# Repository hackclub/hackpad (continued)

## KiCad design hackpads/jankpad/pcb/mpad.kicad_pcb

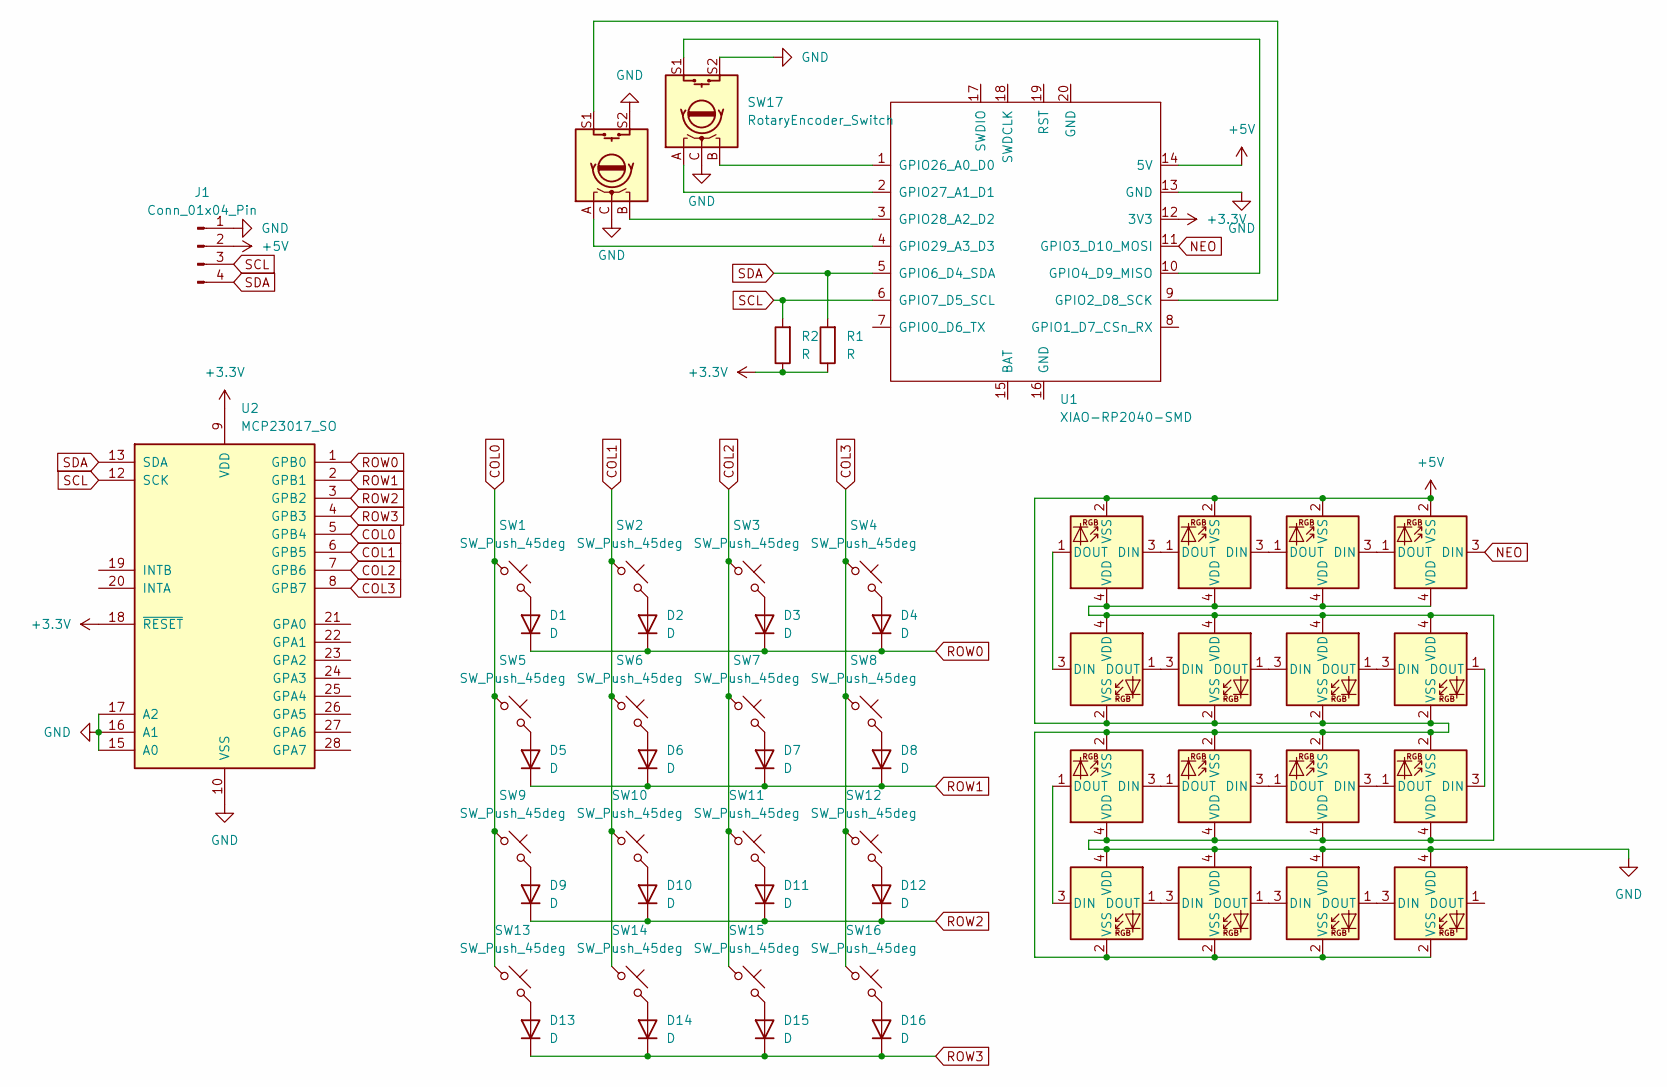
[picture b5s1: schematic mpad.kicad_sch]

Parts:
D1, D2, D3, D4, D5, D6, D7, D8, D9, D10, D11, D12, D13, D14, D15, D16: D; D_DO-35_SOD27_P7.62mm_Horizontal
D17, D18, D19, D20, D21, D22, D23, D24, D25, D26, D27, D28, D29, D30, D31, D32: SK6812MINI; GoofyLED
J1: Conn_01x04_Pin; SSD1306-0.91-OLED-4pin-128x32
R1, R2: R; R_Axial_DIN0204_L3.6mm_D1.6mm_P7.62mm_Horizontal
SW1, SW2, SW3, SW4, SW5, SW6, SW7, SW8, SW9, SW10, SW11, SW12, SW13, SW14, SW15, SW16: SW_Push_45deg; CustomSwitch
SW17, SW18: RotaryEncoder_Switch; RotaryEncoder_Alps_EC11E-Switch_Vertical_H20mm_CircularMoun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
U1: XIAO-RP2040-SMD
U2: MCP23017_SO; SOIC-28W_7.5x17.9mm_P1.27mm

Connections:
+3.3V: R1.1, R2.1, U1.12 (3V3), U2.9 (VDD), U2.18 (~RESET)
+5V: D17.2 (VSS), D18.2 (VSS), D19.2 (VSS), D20.2 (VSS), D21.2 (VSS), D22.2 (VSS), D23.2 (VSS), D24.2 (VSS), D25.2 (VSS), D26.2 (VSS), D27.2 (VSS), D28.2 (VSS), D29.2 (VSS), D30.2 (VSS), D31.2 (VSS), D32.2 (VSS), J1.2, U1.14 (5V)
COL0: SW1.1, SW5.1, SW9.1, SW13.1, U2.5 (GPB4)
COL1: SW2.1, SW6.1, SW10.1, SW14.1, U2.6 (GPB5)
COL2: SW3.1, SW7.1, SW11.1, SW15.1, U2.7 (GPB6)
COL3: SW4.1, SW8.1, SW12.1, SW16.1, U2.8 (GPB7)
GND: D17.4 (VDD), D18.4 (VDD), D19.4 (VDD), D20.4 (VDD), D21.4 (VDD), D22.4 (VDD), D23.4 (VDD), D24.4 (VDD), D25.4 (VDD), D26.4 (VDD), D27.4 (VDD), D28.4 (VDD), D29.4 (VDD), D30.4 (VDD), D31.4 (VDD), D32.4 (VDD), J1.1, SW17.C, SW17.S2, SW18.C, SW18.S2, U1.13 (GND), U2.10 (VSS), U2.15 (A0), U2.16 (A1), U2.17 (A2)
NEO: D17.3 (DIN), U1.11 (GPIO3_D10_MOSI)
unnamed: D1.2 (A), SW1.2
unnamed: D2.2 (A), SW2.2
unnamed: D3.2 (A), SW3.2
unnamed: D4.2 (A), SW4.2
unnamed: D5.2 (A), SW5.2
unnamed: D6.2 (A), SW6.2
unnamed: D7.2 (A), SW7.2
unnamed: D8.2 (A), SW8.2
unnamed: D9.2 (A), SW9.2
unnamed: D10.2 (A), SW10.2
unnamed: D11.2 (A), SW11.2
unnamed: D12.2 (A), SW12.2
unnamed: D13.2 (A), SW13.2
unnamed: D14.2 (A), SW14.2
unnamed: D15.2 (A), SW15.2
unnamed: D16.2 (A), SW16.2
unnamed: D17.1 (DOUT), D18.3 (DIN)
unnamed: D18.1 (DOUT), D19.3 (DIN)
unnamed: D19.1 (DOUT), D20.3 (DIN)
unnamed: D20.1 (DOUT), D21.3 (DIN)
unnamed: D21.1 (DOUT), D22.3 (DIN)
unnamed: D22.1 (DOUT), D23.3 (DIN)
unnamed: D23.1 (DOUT), D24.3 (DIN)
unnamed: D24.1 (DOUT), D25.3 (DIN)
unnamed: D25.1 (DOUT), D26.3 (DIN)
unnamed: D26.1 (DOUT), D27.3 (DIN)
unnamed: D27.1 (DOUT), D28.3 (DIN)
unnamed: D28.1 (DOUT), D29.3 (DIN)
unnamed: D29.1 (DOUT), D30.3 (DIN)
unnamed: D30.1 (DOUT), D31.3 (DIN)
unnamed: D31.1 (DOUT), D32.3 (DIN)
unnamed: SW18.S1, U1.9 (GPIO2_D8_SCK)
unnamed: SW17.S1, U1.10 (GPIO4_D9_MISO)
unnamed: SW17.B, U1.1 (GPIO26_A0_D0)
unnamed: SW17.A, U1.2 (GPIO27_A1_D1)
unnamed: SW18.B, U1.3 (GPIO28_A2_D2)
unnamed: SW18.A, U1.4 (GPIO29_A3_D3)
ROW0: D1.1 (K), D2.1 (K), D3.1 (K), D4.1 (K), U2.1 (GPB0)
ROW1: D5.1 (K), D6.1 (K), D7.1 (K), D8.1 (K), U2.2 (GPB1)
ROW2: D9.1 (K), D10.1 (K), D11.1 (K), D12.1 (K), U2.3 (GPB2)
ROW3: D13.1 (K), D14.1 (K), D15.1 (K), D16.1 (K), U2.4 (GPB3)
SCL: J1.3, R2.2, U1.6 (GPIO7_D5_SCL), U2.12 (SCK)
SDA: J1.4, R1.2, U1.5 (GPIO6_D4_SDA), U2.13 (SDA)

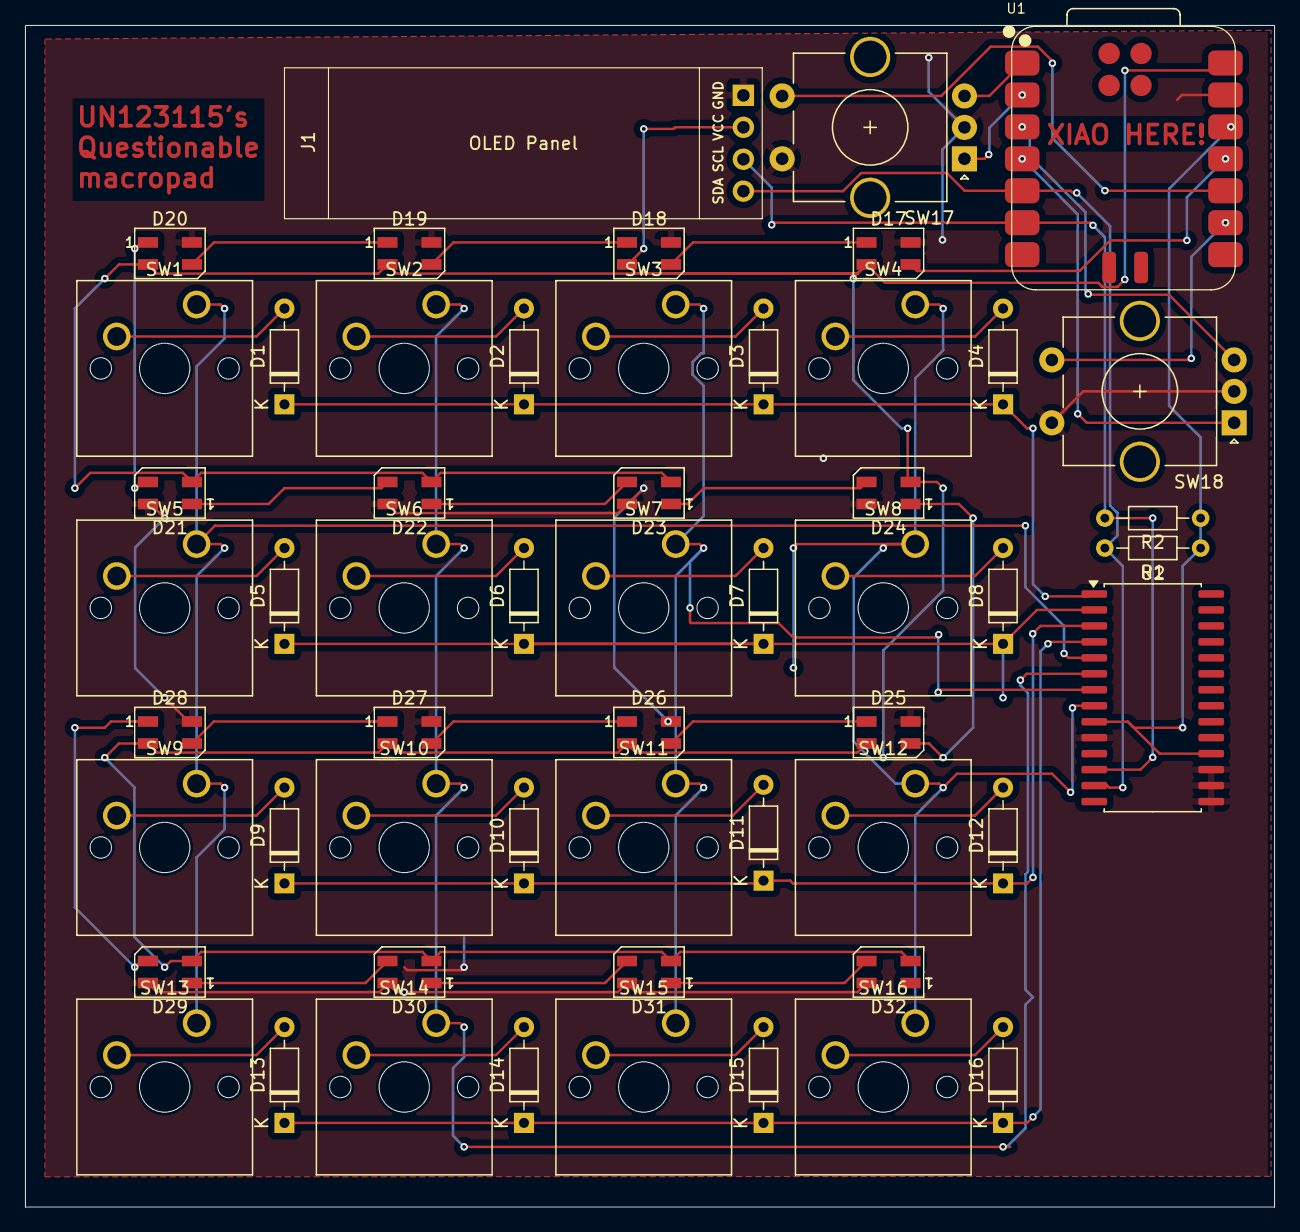
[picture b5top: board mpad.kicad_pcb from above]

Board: 2 copper layers, 99.3 x 94.0 mm, 55 parts (0 on the bottom side), 51 nets.

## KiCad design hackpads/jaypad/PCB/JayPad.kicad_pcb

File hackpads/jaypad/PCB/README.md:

## Components List
| Component                             | Quantity |
|---------------------------------------|----------|
| Cherry MX Switches (TBD in Slack DMs) | 12       |
| Kailh Sockets                         | 12       |
| 500ohm THT Resistor                   | 1        |
| EC11 Rotary Encoder                   | 1        |
| 1N4148W (SOD123)                      | 12       |
| Seeed Studio XIAO RP2040              | 1        |
| WS2812B                               | 8        |
## PCB
White PCB. Should look something like this:

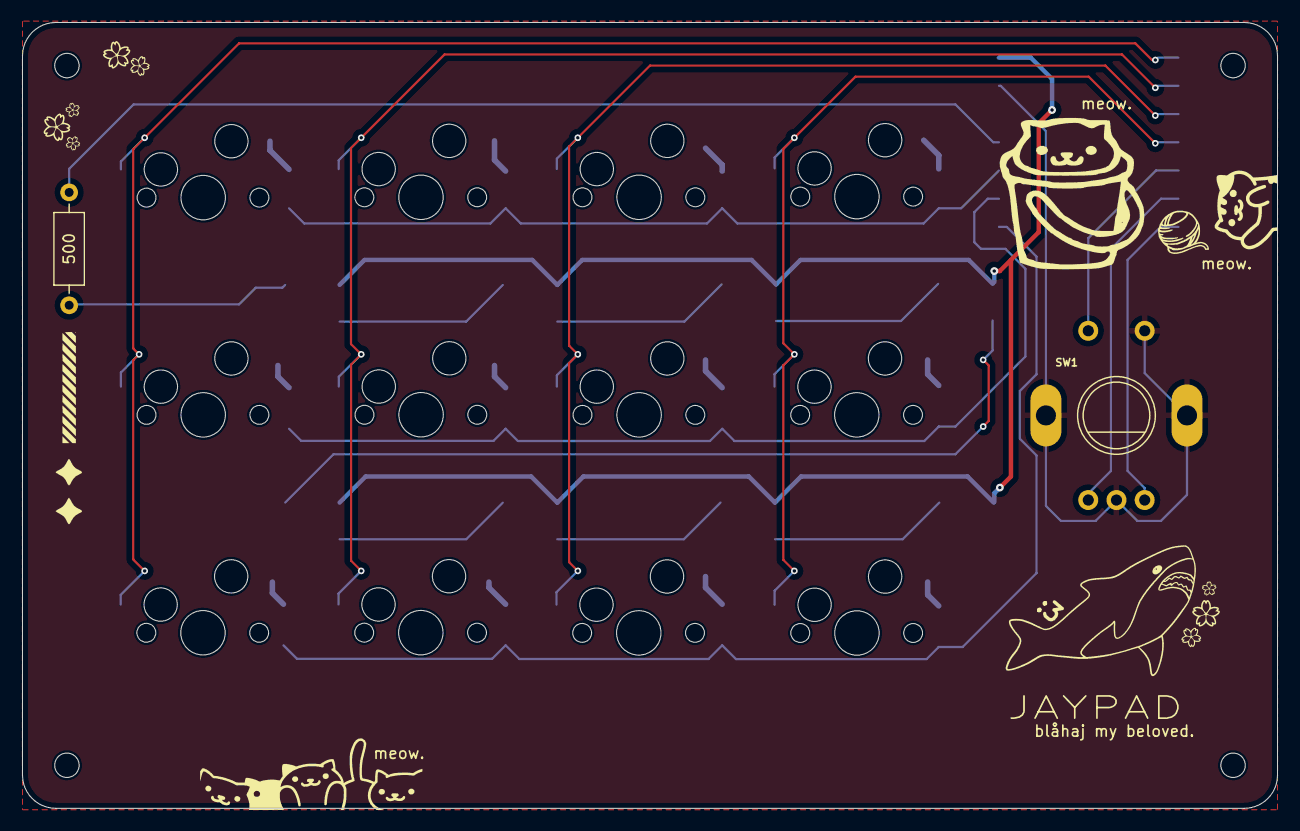
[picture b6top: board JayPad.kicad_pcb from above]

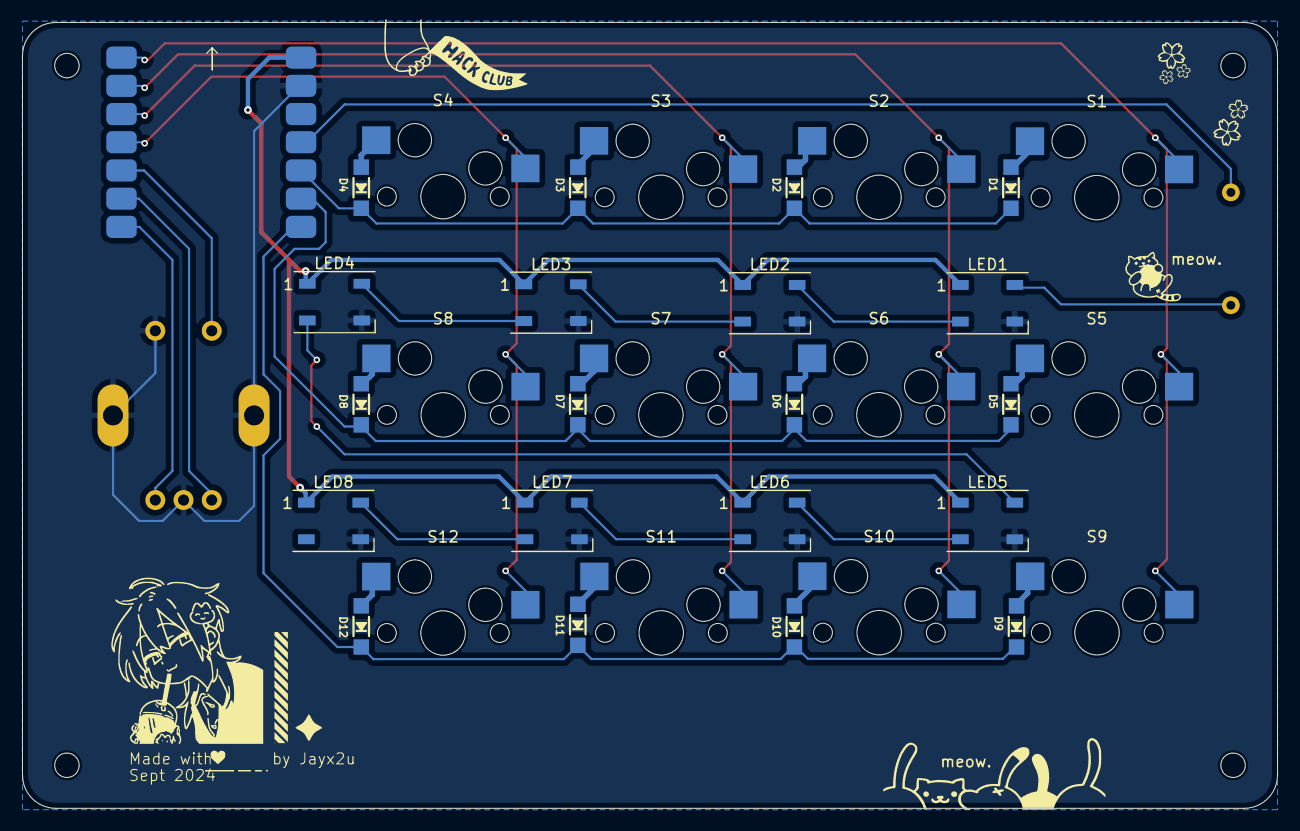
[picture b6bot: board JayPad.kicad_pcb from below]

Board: 2 copper layers, 113.0 x 70.8 mm, 36 parts (21 on the bottom side), 33 nets.

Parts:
:3: LOGO
D1, D2, D3, D4, D5, D6, D7, D8, D9, D10, D11, D12: 1N4148W; MICROBUILDER_SOD-123
LED1, LED2, LED3, LED4, LED5, LED6, LED7, LED8: WS2812B; LED_WS2812B_PLCC4_5.0x5.0mm_P3.2mm
M1: MOUDLE-SEEEDUINO-XIAO; MOUDLE14P-SMD-2.54-21X17.8MM
R1: 500; R_Axial_DIN0207_L6.3mm_D2.5mm_P10.16mm_Horizontal
S1, S2, S3, S4, S5, S6, S7, S8, S9, S10, S11, S12: CherryMX; CherryMX_1.00u_KailhSocket
SW1: PEC11-4215F-S24; ADAFRUIT_ELECTROMECH_PEC11+SWITCH

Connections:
+5V: LED1.1 (VDD), LED2.1 (VDD), LED3.1 (VDD), LED4.1 (VDD), LED5.1 (VDD), LED6.1 (VDD), LED7.1 (VDD), LED8.1 (VDD), M1.14 (5V)
COL0: M1.1 (PA02_A0_D0), S1.1, S5.1, S9.1
COL1: M1.2 (PA4_A1_D1), S2.1, S6.1, S10.1
COL2: M1.3 (PA10_A2_D2), S3.1, S7.1, S11.1
COL3: M1.4 (PA11_A3_D3), S4.1, S8.1, S12.1
DOUT0: LED4.2 (DOUT), LED5.4 (DIN)
ENC_A: M1.6 (PA9_A5_D5_SCL), SW1.P$A
ENC_B: M1.7 (PB08_A6_D6_TX), SW1.P$B
ENC_SW: M1.5 (PA8_A4_D4_SDA), SW1.P$1
GND: LED1.3 (VSS), LED2.3 (VSS), LED3.3 (VSS), LED4.3 (VSS), LED5.3 (VSS), LED6.3 (VSS), LED7.3 (VSS), LED8.3 (VSS), M1.13 (GND), SW1.P$2, SW1.P$C, SW1.P$GND1, SW1.P$GND2
unnamed: D1.A, S1.2
unnamed: D2.A, S2.2
unnamed: D3.A, S3.2
unnamed: D4.A, S4.2
unnamed: D5.A, S5.2
unnamed: D6.A, S6.2
unnamed: D7.A, S7.2
unnamed: D8.A, S8.2
unnamed: D9.A, S9.2
unnamed: D10.A, S10.2
unnamed: D11.A, S11.2
unnamed: D12.A, S12.2
unnamed: LED3.2 (DOUT), LED4.4 (DIN)
unnamed: LED2.2 (DOUT), LED3.4 (DIN)
unnamed: LED1.2 (DOUT), LED2.4 (DIN)
unnamed: LED1.4 (DIN), R1.2
unnamed: LED5.2 (DOUT), LED6.4 (DIN)
unnamed: LED6.2 (DOUT), LED7.4 (DIN)
unnamed: LED7.2 (DOUT), LED8.4 (DIN)
RGB: M1.11 (PA6_A10_D10_MOSI), R1.1
ROW0: D1.C, D2.C, D3.C, D4.C, M1.10 (PA5_A9_D9_MISO)
ROW1: D5.C, D6.C, D7.C, D8.C, M1.9 (PA7_A8_D8_SCK)
ROW2: D9.C, D10.C, D11.C, D12.C, M1.8 (PB09_A7_D7_RX)

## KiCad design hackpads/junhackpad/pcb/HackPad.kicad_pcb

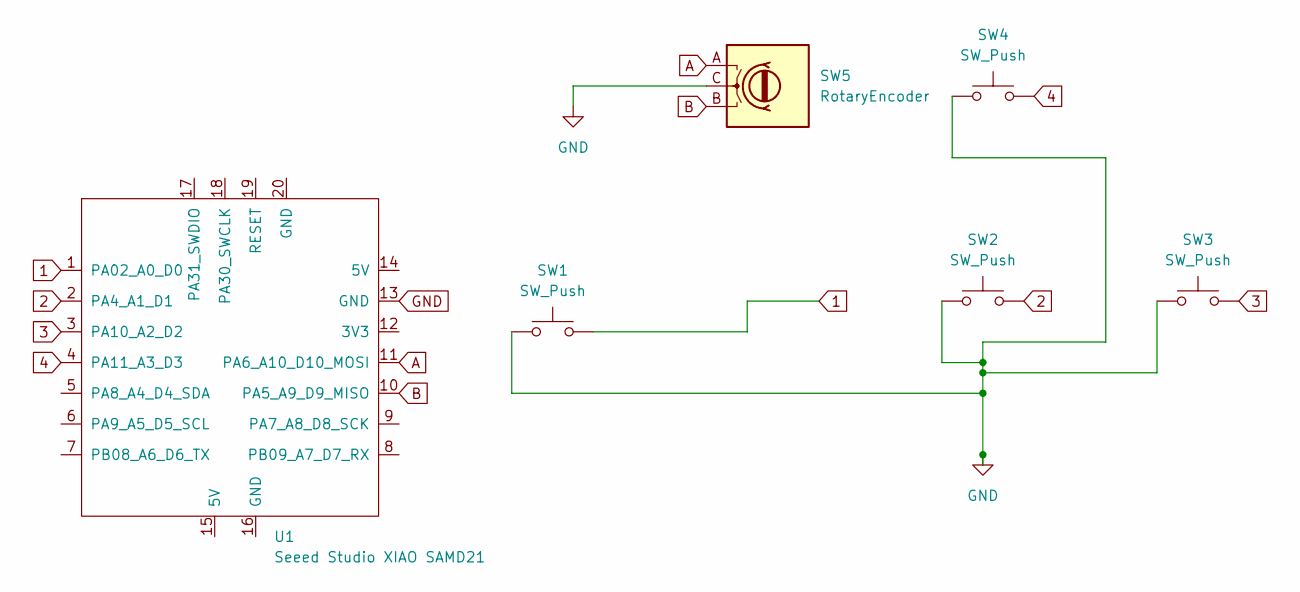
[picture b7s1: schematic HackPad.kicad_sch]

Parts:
SW1, SW2, SW3, SW4: SW_Push; SW_Cherry_MX_1.00u_PCB
SW5: RotaryEncoder; RotaryEncoder_Alps_EC11E-Switch_Vertical_H20mm
U1: Seeed Studio XIAO SAMD21; XIAO-Generic-Thruhole-14P-2.54-21X17.8MM

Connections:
1: SW1.2, U1.1 (PA02_A0_D0)
2: SW2.2, U1.2 (PA4_A1_D1)
3: SW3.2, U1.3 (PA10_A2_D2)
4: SW4.2, U1.4 (PA11_A3_D3)
A: SW5.A, U1.11 (PA6_A10_D10_MOSI)
B: SW5.B, U1.10 (PA5_A9_D9_MISO)
GND: SW1.1, SW2.1, SW3.1, SW4.1, SW5.C, U1.13 (GND)

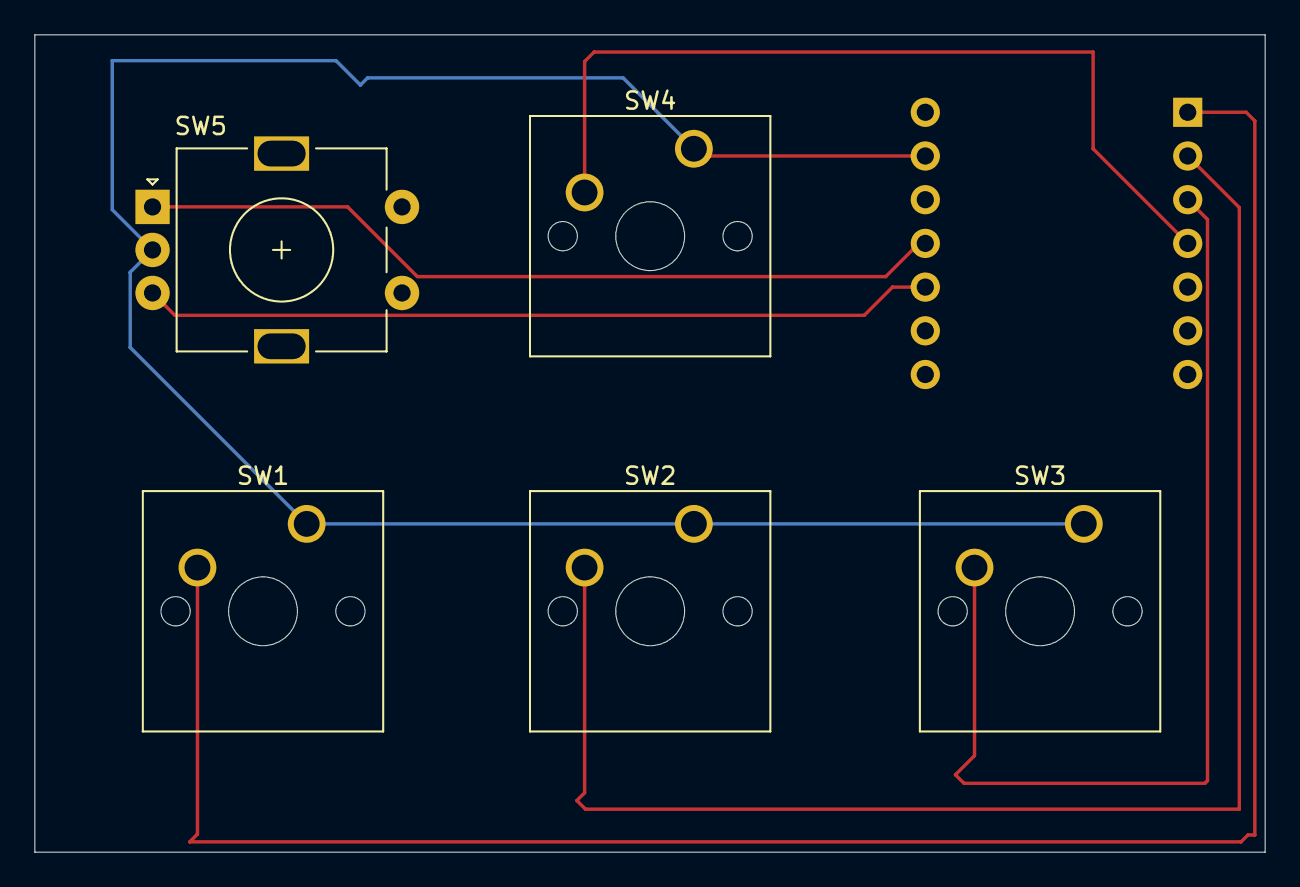
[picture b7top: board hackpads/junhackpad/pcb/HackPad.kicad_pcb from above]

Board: 2 copper layers, 71.5 x 47.5 mm, 6 parts (1 on the bottom side), 7 nets.
